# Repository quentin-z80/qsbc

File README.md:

# qsbc

## Specs

- i.MX8M Mini 4x 1.8GHz ARM Cortex-A53
- 4GB LPDDR4
- 4MB QSPI Flash
- 64GB eMMC
- M.2 2230 Slot
- MicroSD card slot
- 2x USB Type-C DRP
- USB Type-C Power in
- USB Type-C debug port
- 10/100/1000 Ethernet
- Displayport output

## Flashing u-boot

1. Get `u-boot`

    ```
    git clone https://gitlab.com/quentin-z80/u-boot.git
    ```

2. Build `TF-A`

    ```
    git clone https://git.trustedfirmware.org/TF-A/trusted-firmware-a.git
    cd trusted-firmware-a
    TF_LDFLAGS="--no-warn-rwx-segment" make plat=imx8mm bl31
    cp build/imx8mm/release/bl31.bin ../u-boot/
    ```

3. Get i.MX8MM DDR Firmware

    ```
    wget https://www.nxp.com/lgfiles/NMG/MAD/YOCTO/firmware-imx-8.9.bin
    chmod +x firmware-imx-8.9.bin
    ./firmware-imx-8.9.bin
    cp firmware-imx-8.9/firmware/ddr/synopsys/lpddr4*.bin u-boot/
    ```

4. Build `u-boot` for SD card boot

    ```
    cd u-boot
    export CROSS_COMPILE=aarch64-linux-gnu- ARCH=arm64
    make qsbc_imx8mm_defconfig
    make
    sudo dd if=flash.bin of=/dev/mmcblk0 bs=1024 seek=32 conv=notrunc
    ```

5. Flash and boot `u-boot` from sd card

    ```
    sudo dd if=flash.bin of=/dev/mmcblk0 bs=1024 seek=32 conv=notrunc
    sudo tio -b 115200 /dev/ttyACM0
    ```

6. Build `u-boot` for QSPI boot

    ```
    make qsbc_imx8mm_fspi_defconfig
    make
    ```

7. Flash `u-boot` to QSPI

    ```
    u-boot=> run dfuspi
    sudo dfu-util -D flash.bin
    ```

## TODO

- USB-UART ICs need to have VDDIO derived from USB VBUS so they do not reset
on board reset (or find a different ic)

- USB VBUS fault pins need to be connected to usb phy oc pads, not gpio pins

- UART1 TXO is connected to the wrong pad

- Test displayport out, waiting for better sn65dsi86 avalability

- optimize bom, replace 0201s with 0402s where there is space / no si limitations

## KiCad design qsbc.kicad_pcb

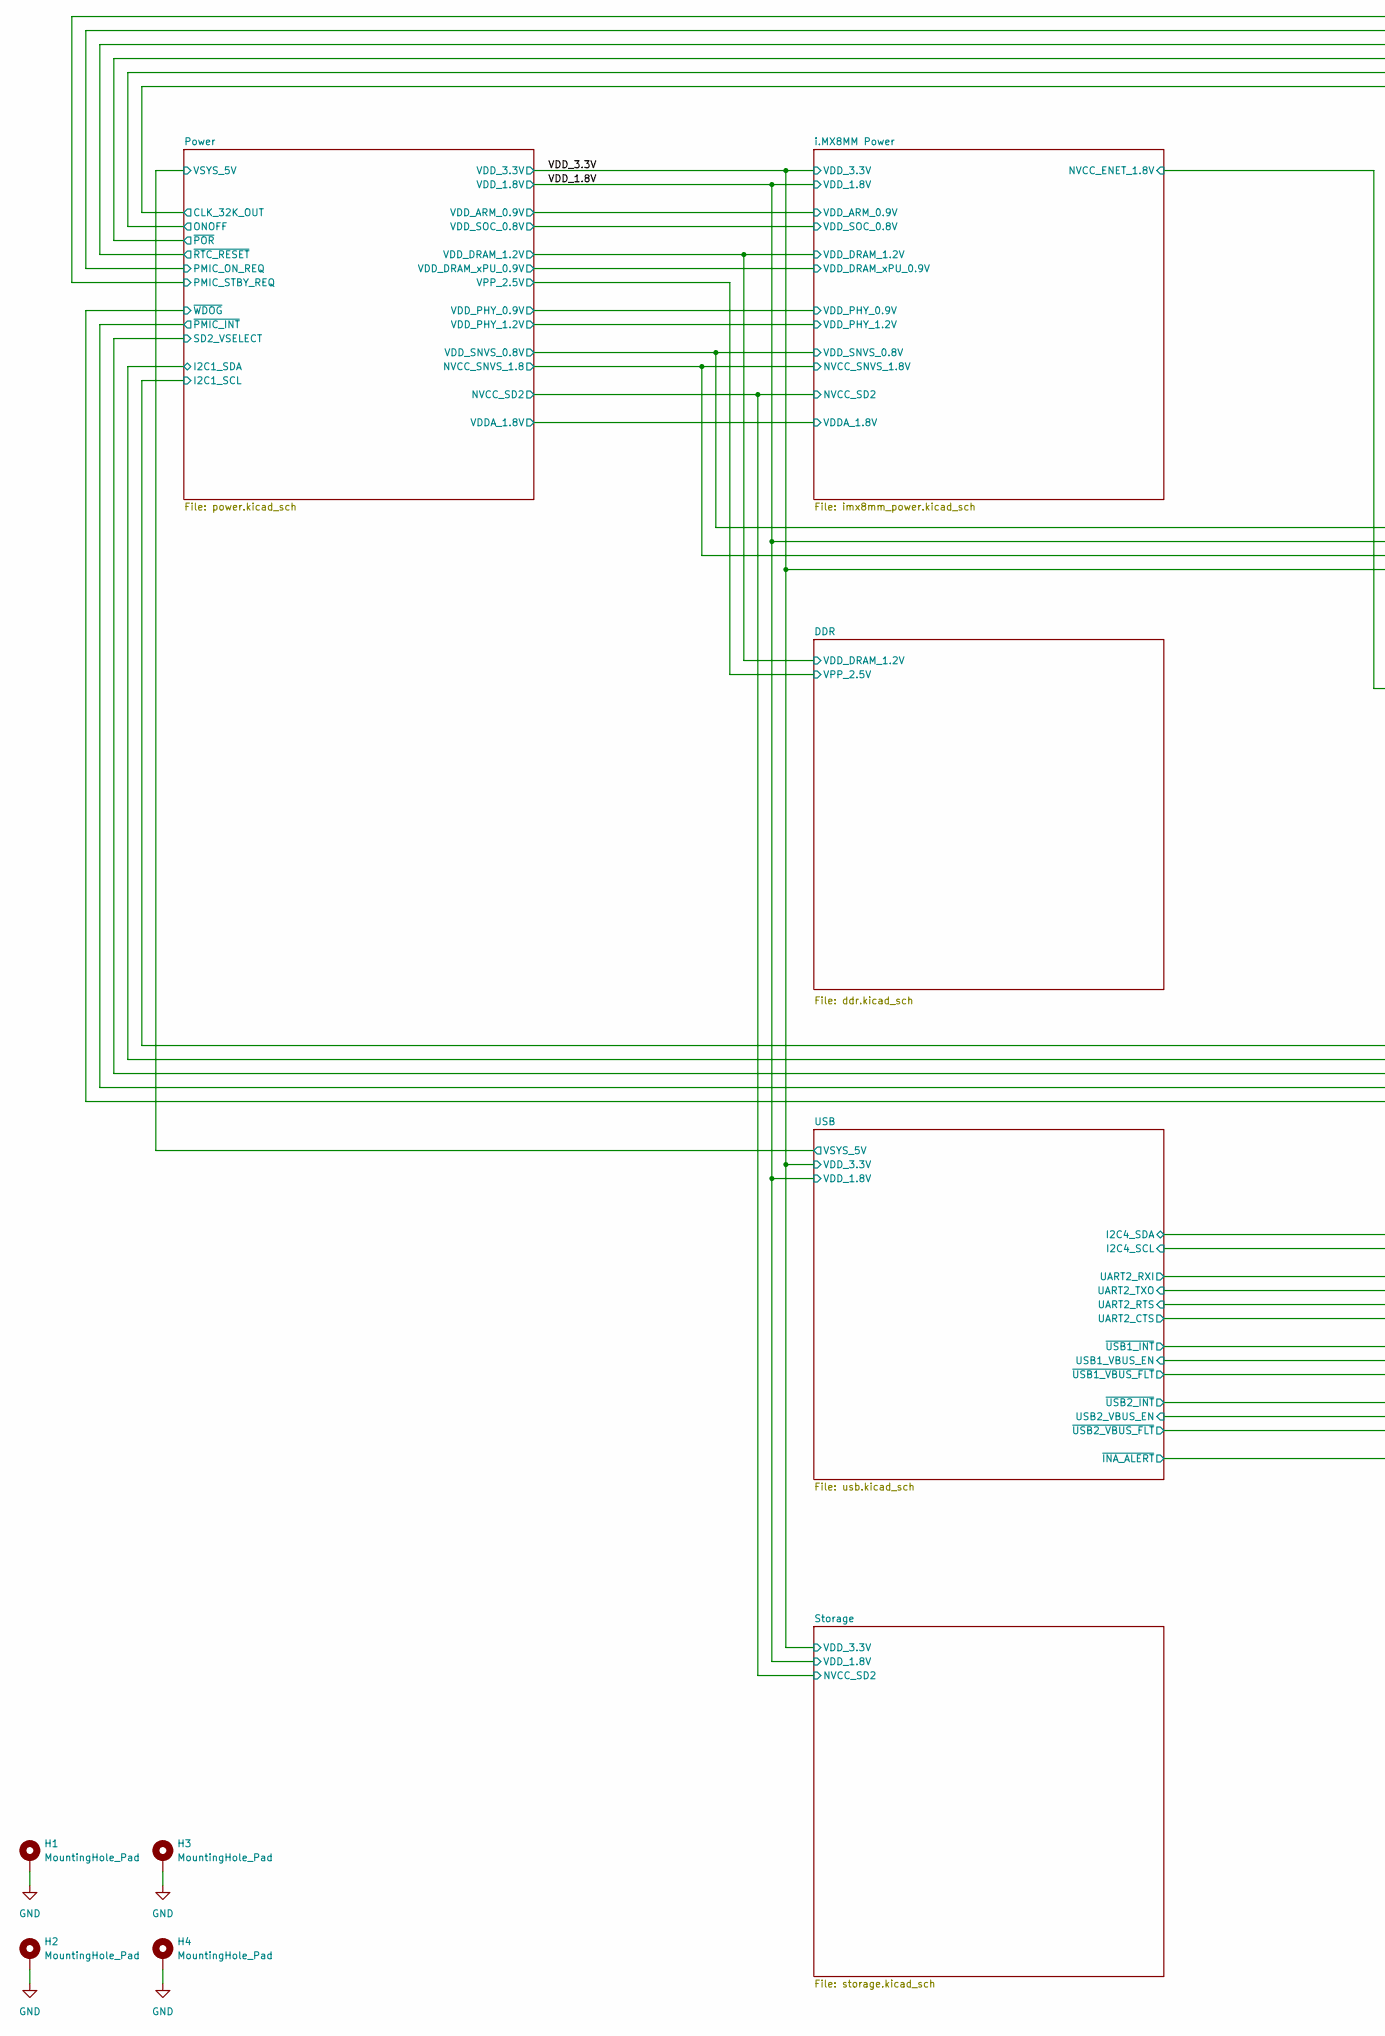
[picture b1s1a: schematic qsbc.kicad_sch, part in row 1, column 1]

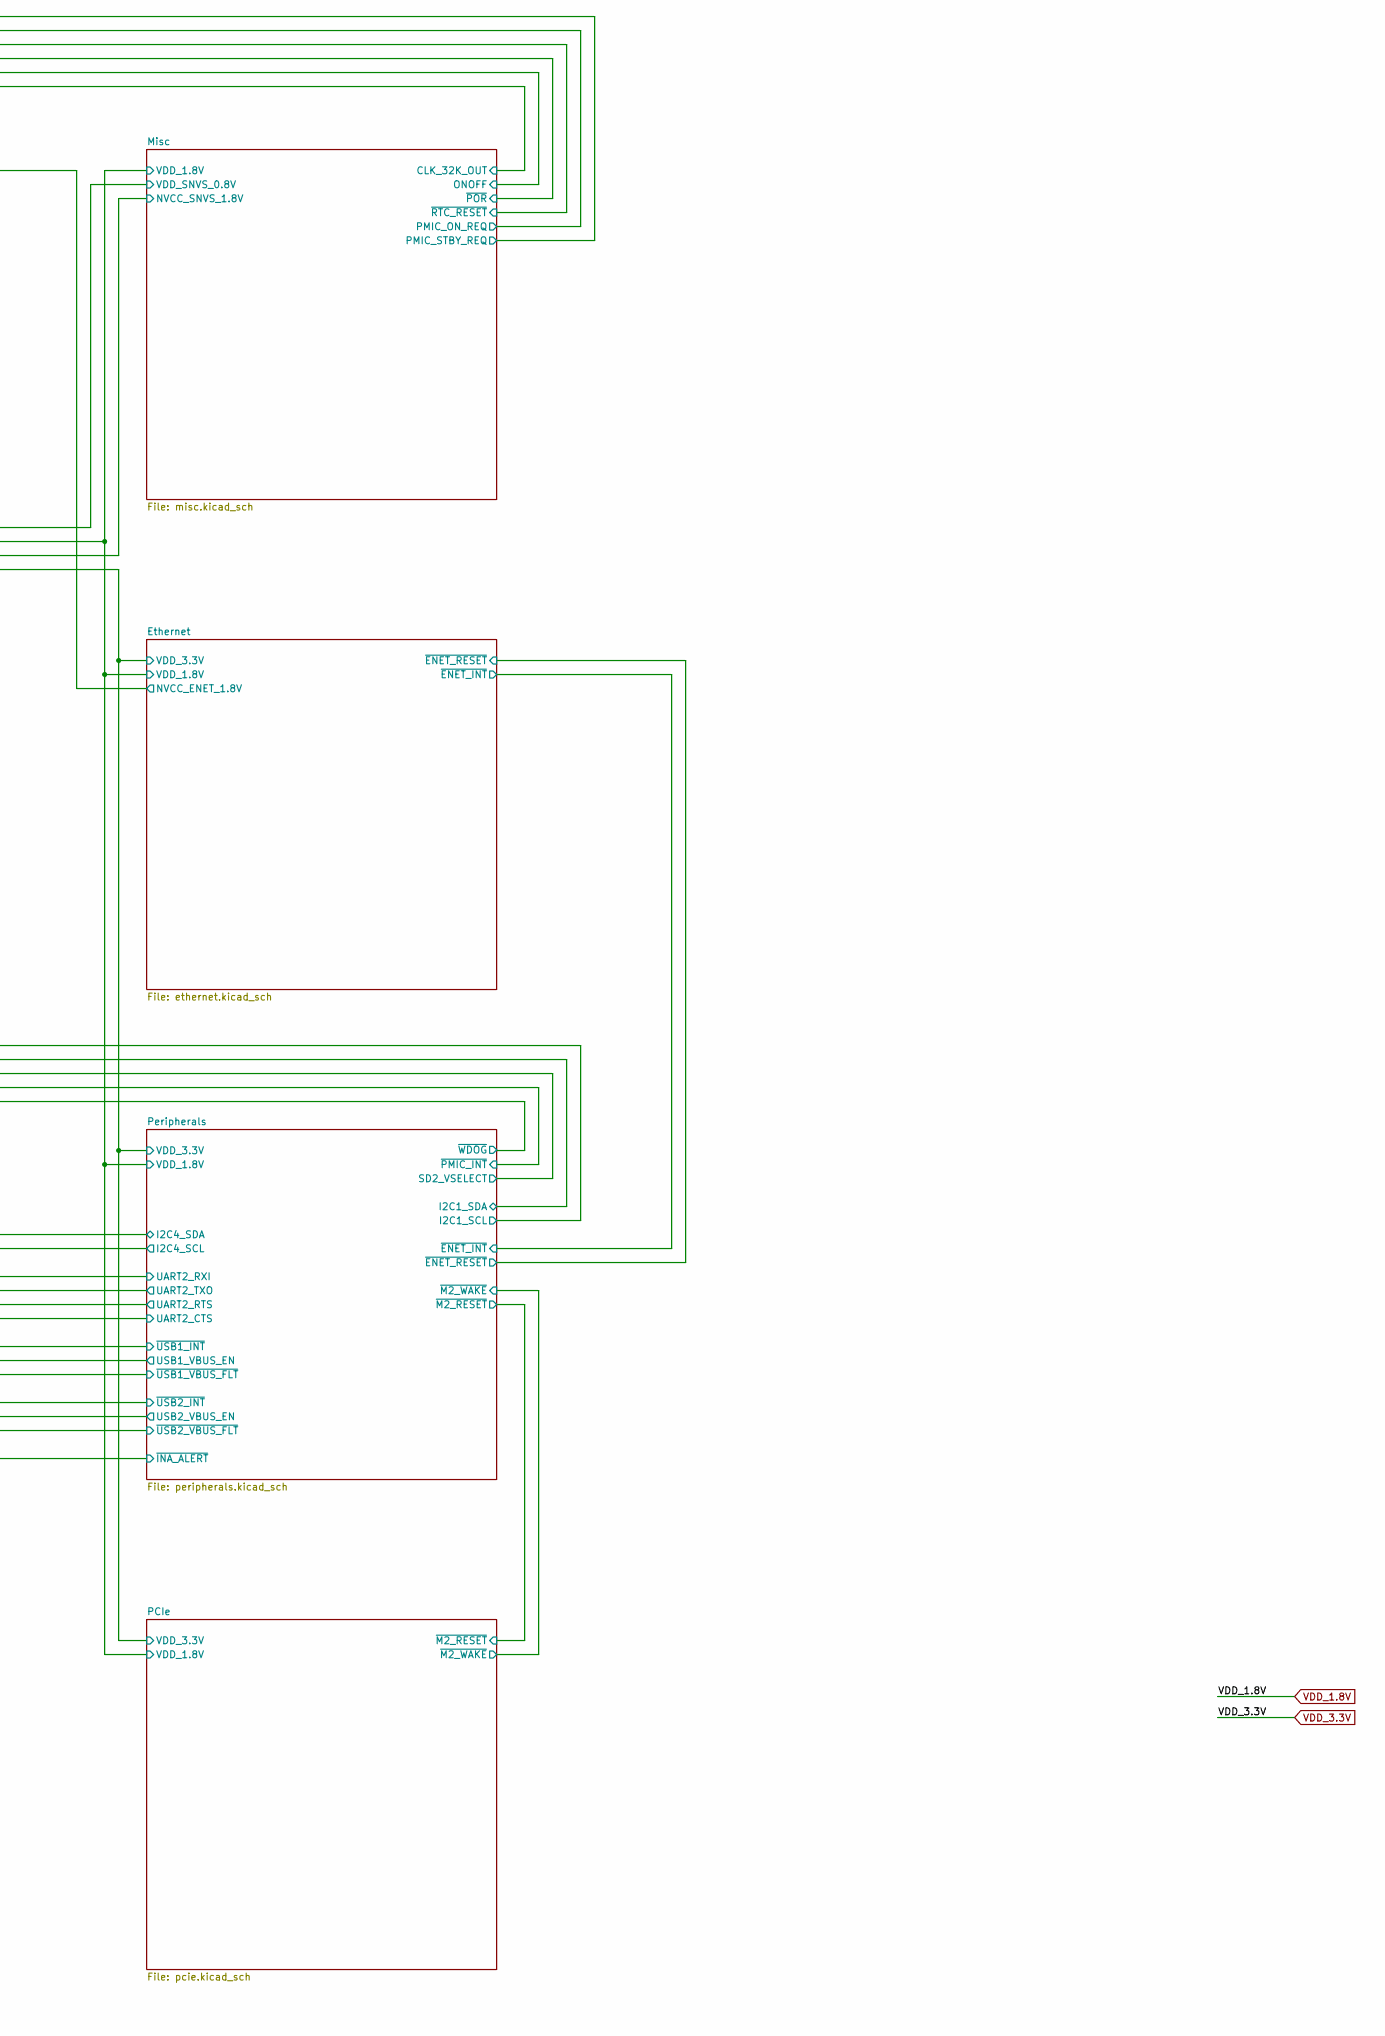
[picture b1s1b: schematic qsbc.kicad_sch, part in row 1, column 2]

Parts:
H1, H2, H3, H4: MountingHole_Pad; MountingHole_3.2mm_M3_Pad_Via

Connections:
GND: H1.1, H2.1, H3.1, H4.1; also elsewhere on the board

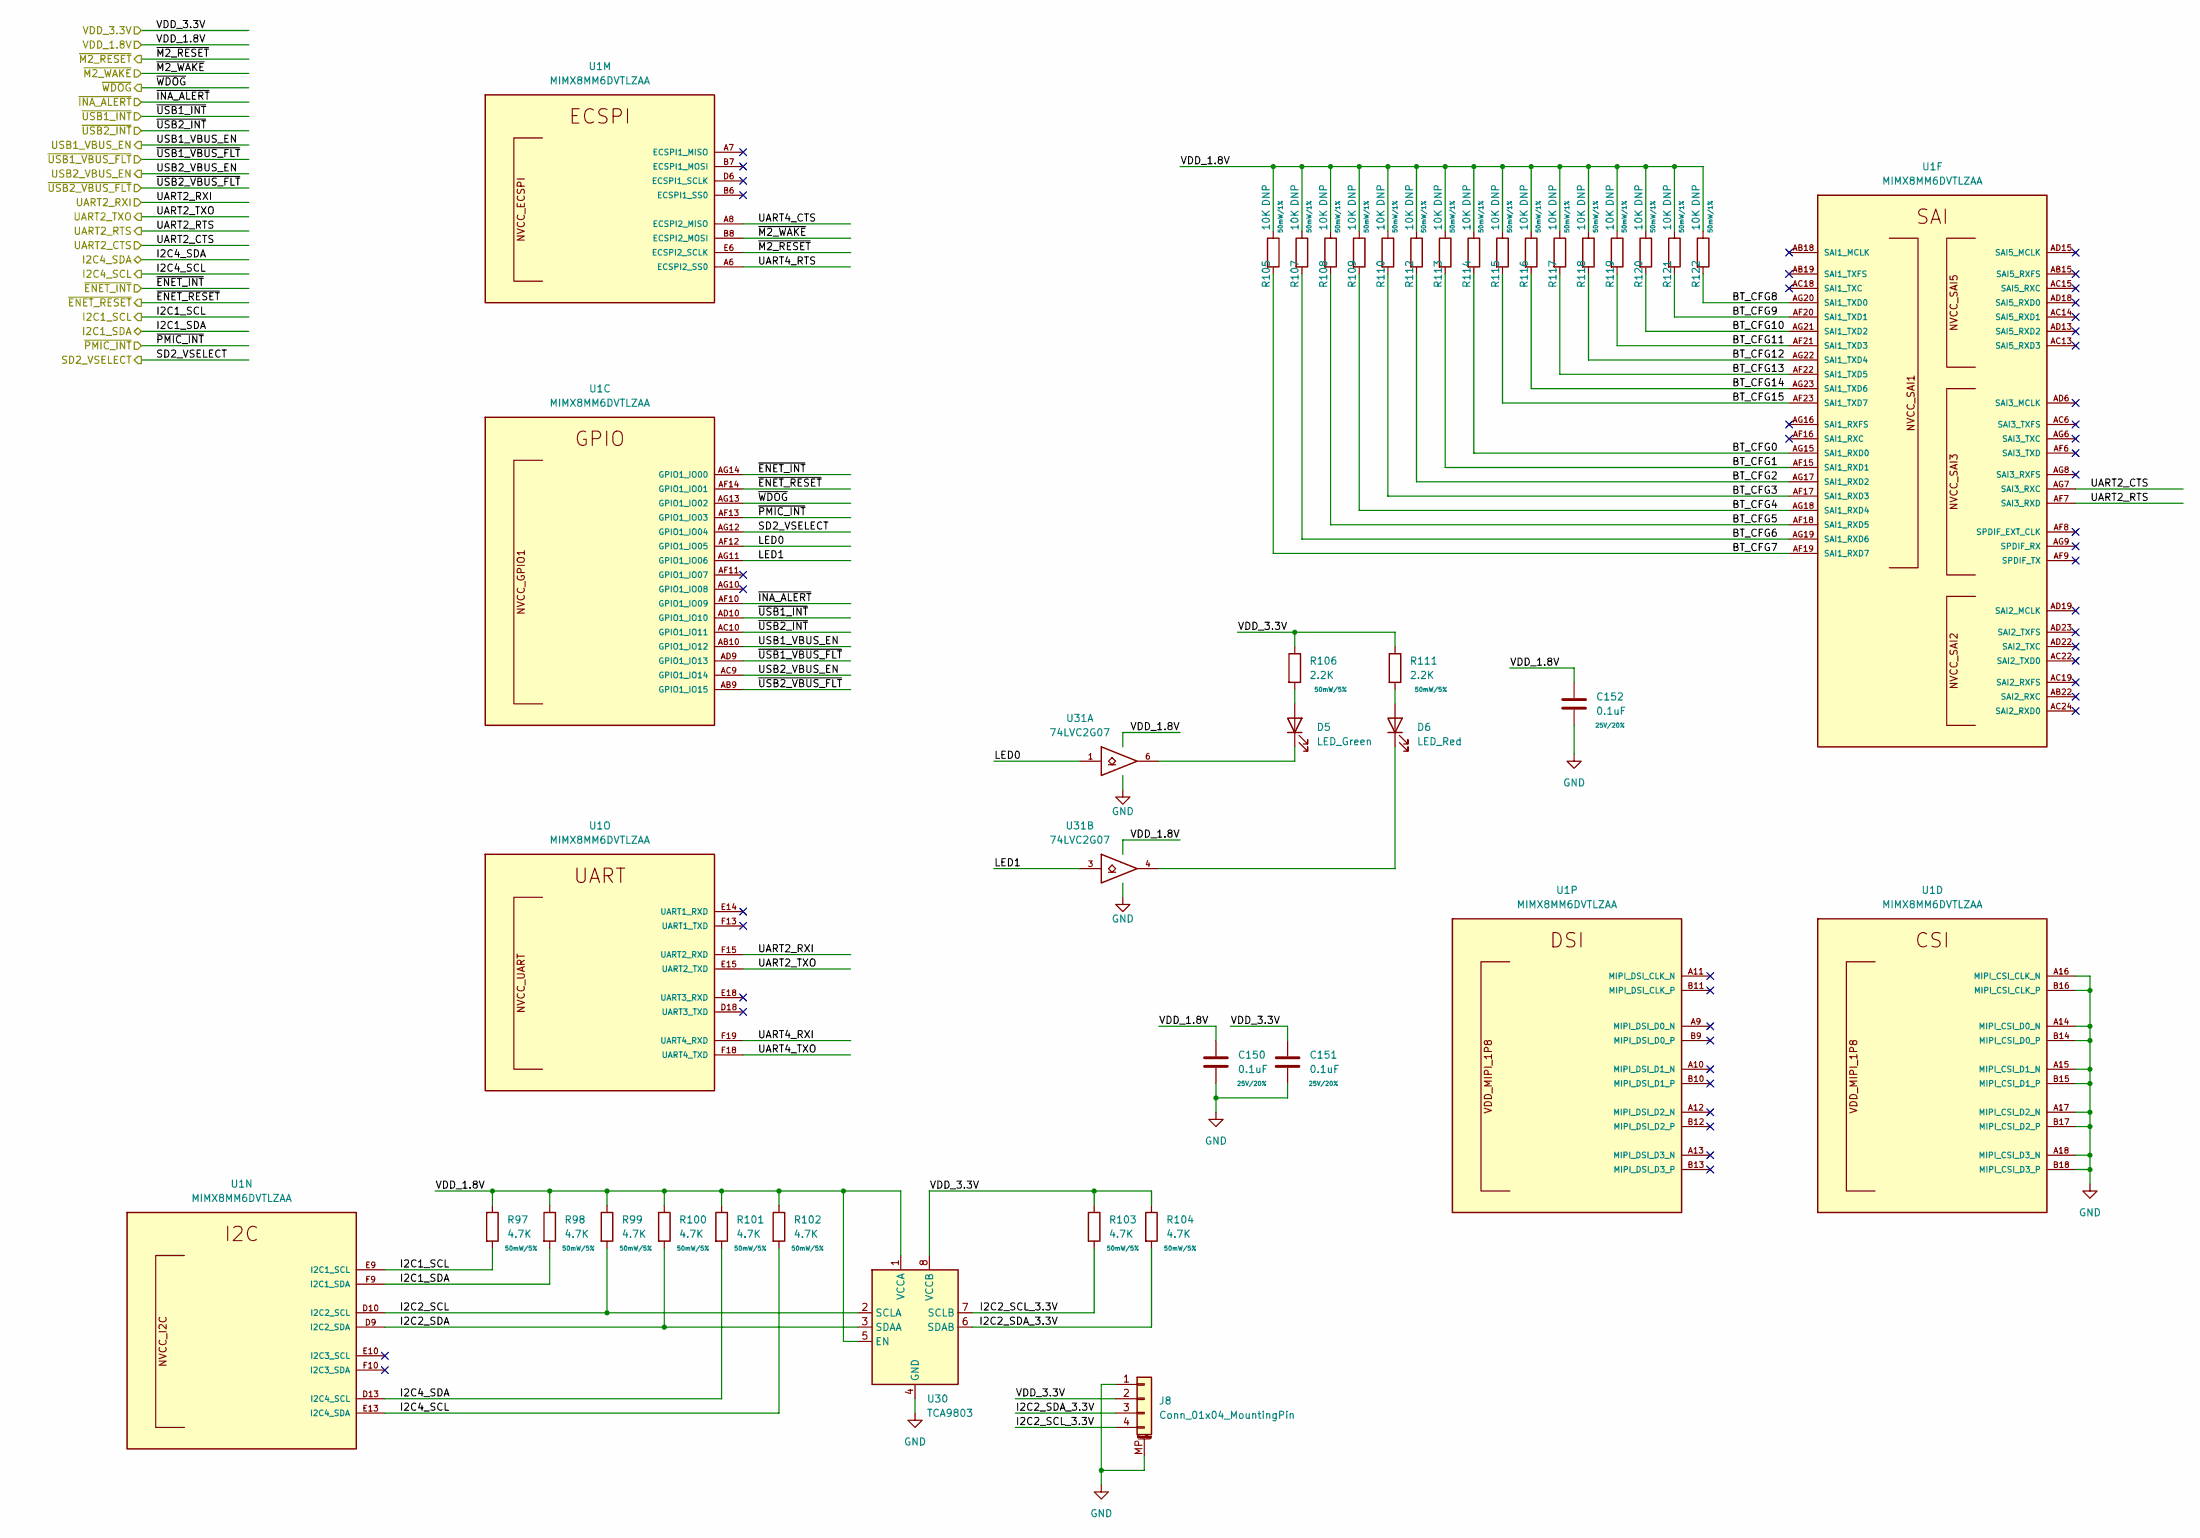
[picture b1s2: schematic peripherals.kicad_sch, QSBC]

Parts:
C150, C151, C152: 0.1uF; C_0402_1005Metric; Rating 25V/20%
D5: LED_Green; LED_0603_1608Metric
D6: LED_Red; LED_0603_1608Metric
J8: Conn_01x04_MountingPin; JST_SH_SM04B-SRSS-TB_1x04-1MP_P1.00mm_Horizontal
R97, R98, R99, R100, R101, R102, R103, R104: 4.7K; R_0402_1005Metric; Rating 50mW/5%
R105, R107, R108, R109, R110, R112, R113, R114, R115, R116, R117, R118, R119, R120, R121, R122: 10K; R_0402_1005Metric; Rating 50mW/1%; MPN RC0402JR-0710KL; DigiKey_PN 311-10KJRCT-ND
R106, R111: 2.2K; R_0402_1005Metric; Rating 50mW/5%
U1: MIMX8MM6DVTLZAA; SOT1967-1
U30: TCA9803; VSSOP-8_3.0x3.0mm_P0.65mm
U31: 74LVC2G07; SOT-886

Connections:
/Ethernet/~ENET_INT: U1.AG14 (GPIO1_IO00); also elsewhere on the board
/Ethernet/~ENET_RESET: U1.AF14 (GPIO1_IO01); also elsewhere on the board
/PCIe/~M2_RESET: U1.E6 (ECSPI2_SCLK); also elsewhere on the board
/PCIe/~M2_WAKE: U1.B8 (ECSPI2_MOSI); also elsewhere on the board
/Peripherals/BT_CFG0: R114.2, U1.AG15 (SAI1_RXD0)
/Peripherals/BT_CFG1: R113.2, U1.AF15 (SAI1_RXD1)
/Peripherals/BT_CFG2: R112.2, U1.AG17 (SAI1_RXD2)
/Peripherals/BT_CFG3: R110.2, U1.AF17 (SAI1_RXD3)
/Peripherals/BT_CFG4: R109.2, U1.AG18 (SAI1_RXD4)
/Peripherals/BT_CFG5: R108.2, U1.AF18 (SAI1_RXD5)
/Peripherals/BT_CFG6: R107.2, U1.AG19 (SAI1_RXD6)
/Peripherals/BT_CFG7: R105.2, U1.AF19 (SAI1_RXD7)
/Peripherals/BT_CFG8: R122.2, U1.AG20 (SAI1_TXD0)
/Peripherals/BT_CFG9: R121.2, U1.AF20 (SAI1_TXD1)
/Peripherals/BT_CFG10: R120.2, U1.AG21 (SAI1_TXD2)
/Peripherals/BT_CFG11: R119.2, U1.AF21 (SAI1_TXD3)
/Peripherals/BT_CFG12: R118.2, U1.AG22 (SAI1_TXD4)
/Peripherals/BT_CFG13: R117.2, U1.AF22 (SAI1_TXD5)
/Peripherals/BT_CFG14: R116.2, U1.AG23 (SAI1_TXD6)
/Peripherals/BT_CFG15: R115.2, U1.AF23 (SAI1_TXD7)
/Peripherals/I2C1_SCL: R97.2, U1.E9 (I2C1_SCL); also elsewhere on the board
/Peripherals/I2C1_SDA: R98.2, U1.F9 (I2C1_SDA); also elsewhere on the board
/Peripherals/I2C2_SCL: R99.2, U1.D10 (I2C2_SCL), U30.2 (SCLA)
/Peripherals/I2C2_SCL_3.3V: J8.4, R103.2, U30.7 (SCLB)
/Peripherals/I2C2_SDA: R100.2, U1.D9 (I2C2_SDA), U30.3 (SDAA)
/Peripherals/I2C2_SDA_3.3V: J8.3, R104.2, U30.6 (SDAB)
/Peripherals/I2C4_SCL: R102.2, U1.E13 (I2C4_SDA); also elsewhere on the board
/Peripherals/I2C4_SDA: R101.2, U1.D13 (I2C4_SCL); also elsewhere on the board
/Peripherals/LED0: U1.AF12 (GPIO1_IO05), U31.1
/Peripherals/LED1: U1.AG11 (GPIO1_IO06), U31.3
/Peripherals/SD2_VSELECT: U1.AG12 (GPIO1_IO04); also elsewhere on the board
/Peripherals/UART2_CTS: U1.AG7 (SAI3_RXC); also elsewhere on the board
/Peripherals/UART2_RTS: U1.AF7 (SAI3_RXD); also elsewhere on the board
/Peripherals/UART2_RXI: U1.F15 (UART2_RXD); also elsewhere on the board
/Peripherals/UART2_TXO: U1.E15 (UART2_TXD); also elsewhere on the board
/Peripherals/UART4_CTS: U1.A8 (ECSPI2_MISO)
/Peripherals/UART4_RTS: U1.A6 (ECSPI2_SS0)
/Peripherals/UART4_RXI: U1.F19 (UART4_RXD)
/Peripherals/UART4_TXO: U1.F18 (UART4_TXD)
/Peripherals/USB1_VBUS_EN: U1.AB10 (GPIO1_IO12); also elsewhere on the board
/Peripherals/USB2_VBUS_EN: U1.AC9 (GPIO1_IO14); also elsewhere on the board
/Peripherals/~INA_ALERT: U1.AF10 (GPIO1_IO09); also elsewhere on the board
/Peripherals/~PMIC_INT: U1.AF13 (GPIO1_IO03); also elsewhere on the board
/Peripherals/~USB1_INT: U1.AD10 (GPIO1_IO10); also elsewhere on the board
/Peripherals/~USB1_VBUS_FLT: U1.AD9 (GPIO1_IO13); also elsewhere on the board
/Peripherals/~USB2_INT: U1.AC10 (GPIO1_IO11); also elsewhere on the board
/Peripherals/~USB2_VBUS_FLT: U1.AB9 (GPIO1_IO15); also elsewhere on the board
/Peripherals/~WDOG: U1.AG13 (GPIO1_IO02)
GND: C150.2, C151.2, C152.2, J8.1, J8.MP (MountPin), U1.A14 (MIPI_CSI_D0_N), U1.A15 (MIPI_CSI_D1_N), U1.A16 (MIPI_CSI_CLK_N), U1.A17 (MIPI_CSI_D2_N), U1.A18 (MIPI_CSI_D3_N), U1.B14 (MIPI_CSI_D0_P), U1.B15 (MIPI_CSI_D1_P), U1.B16 (MIPI_CSI_CLK_P), U1.B17 (MIPI_CSI_D2_P), U1.B18 (MIPI_CSI_D3_P), U30.4 (GND), U31.2 (GND); also elsewhere on the board
unnamed: D5.1 (K), U31.6
unnamed: D5.2 (A), R106.2
unnamed: D6.1 (K), U31.4
unnamed: D6.2 (A), R111.2
VDD_1.8V: C150.1, C152.1, R97.1, R98.1, R99.1, R100.1, R101.1, R102.1, R105.1, R107.1, R108.1, R109.1, R110.1, R112.1, R113.1, R114.1, R115.1, R116.1, R117.1, R118.1, R119.1, R120.1, R121.1, R122.1, U30.1 (VCCA), U30.5 (EN), U31.5 (VCC); also elsewhere on the board
VDD_3.3V: C151.1, J8.2, R103.1, R104.1, R106.1, R111.1, U30.8 (VCCB); also elsewhere on the board

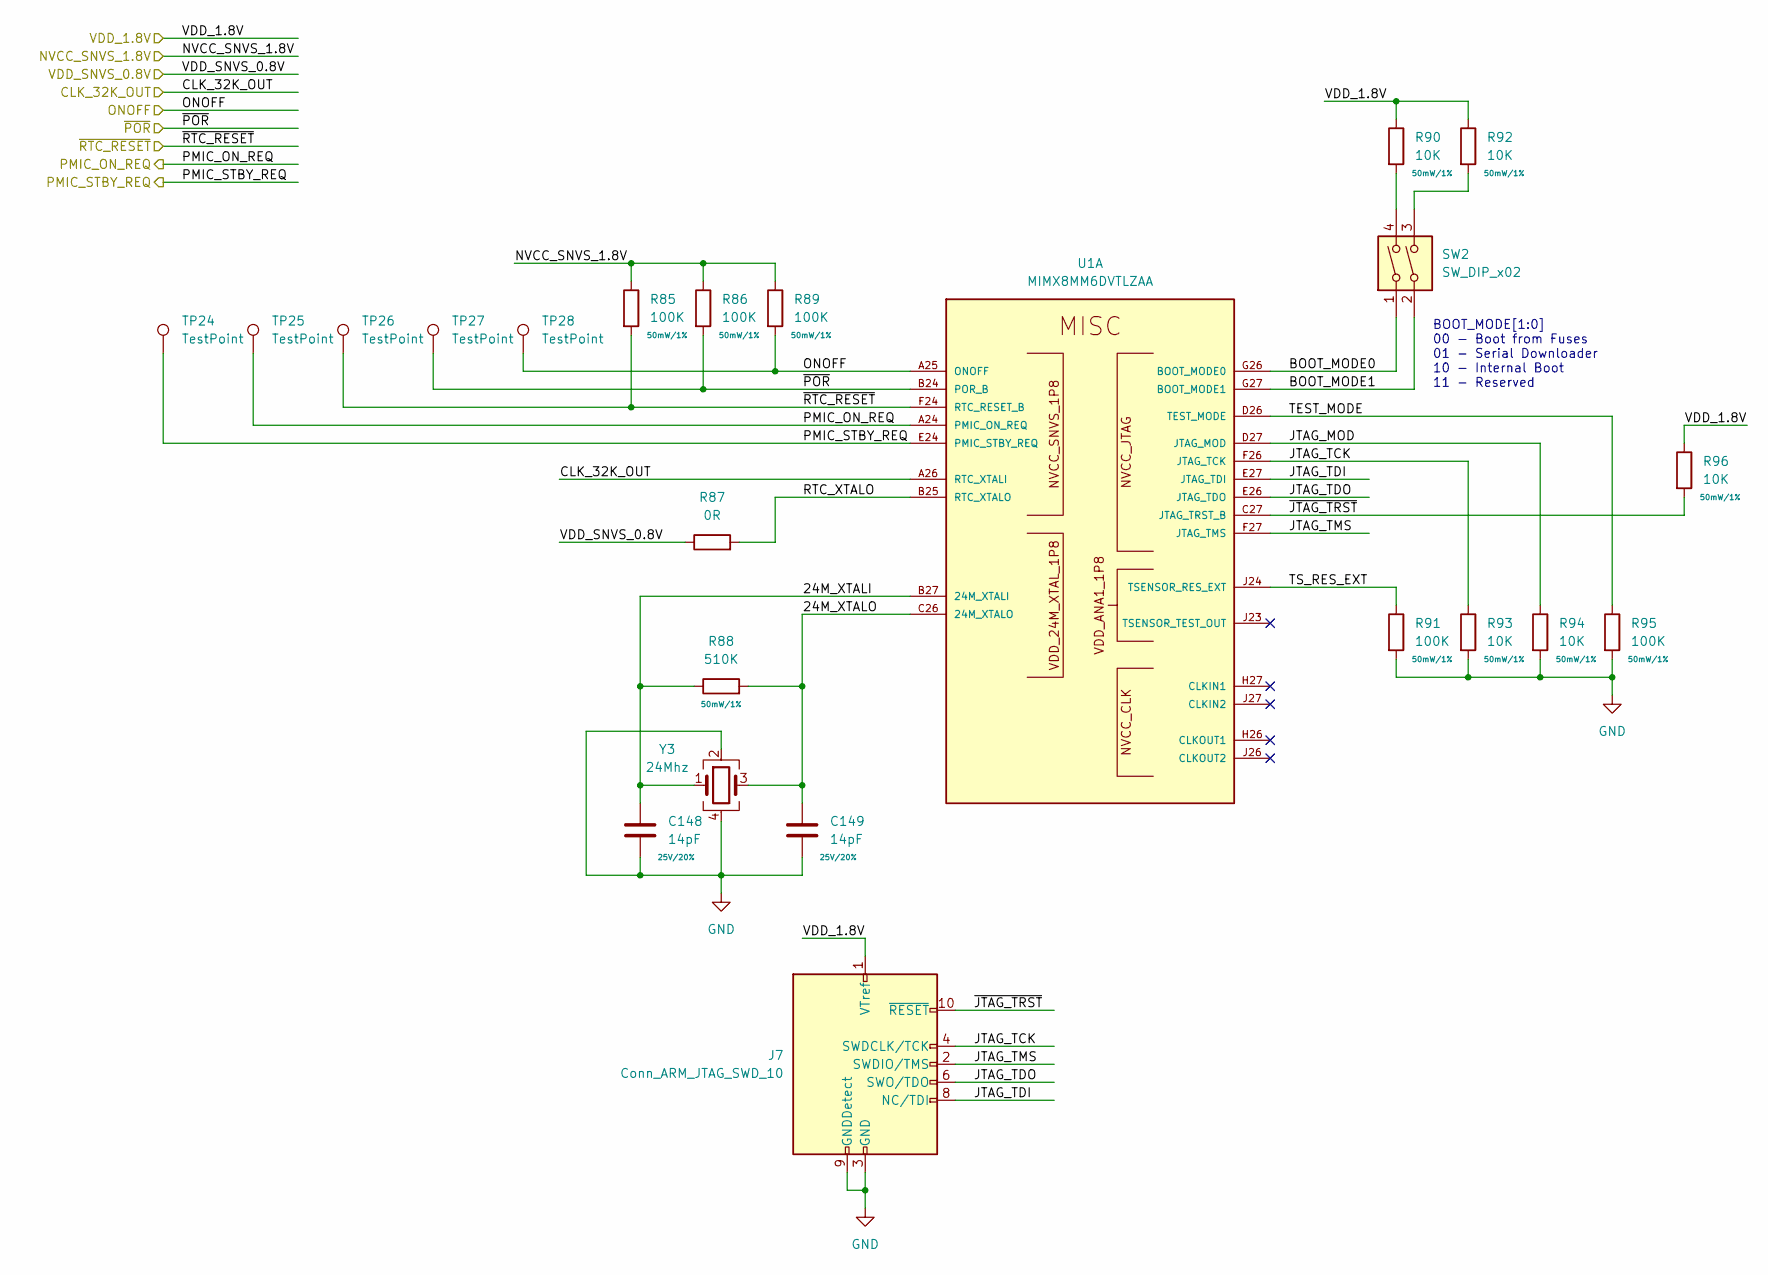
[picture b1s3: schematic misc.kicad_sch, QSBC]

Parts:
C148, C149: 14pF; C_0402_1005Metric; Rating 25V/20%
J7: Conn_ARM_JTAG_SWD_10; PinHeader_2x05_P1.27mm_Vertical
R85, R86, R89, R91, R95: 100K; R_0402_1005Metric; Rating 50mW/1%
R87: 0R; R_0402_1005Metric
R88: 510K; R_0402_1005Metric; Rating 50mW/1%
R90, R92, R93, R94, R96: 10K; R_0402_1005Metric; Rating 50mW/1%
SW2: SW_DIP_x02; DHN-02
TP24, TP25, TP26, TP27, TP28: TestPoint; TestPoint_Pad_D1.0mm
U1: MIMX8MM6DVTLZAA; SOT1967-1
Y3: 24Mhz; Crystal_SMD_3225-4Pin_3.2x2.5mm; MPN ECS-240-10-33B-7KM-TR

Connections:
/Misc/24M_XTALI: C148.1, R88.1, U1.B27 (24M_XTALI), Y3.1
/Misc/24M_XTALO: C149.1, R88.2, U1.C26 (24M_XTALO), Y3.3
/Misc/BOOT_MODE0: SW2.1, U1.G26 (BOOT_MODE0)
/Misc/BOOT_MODE1: SW2.2, U1.G27 (BOOT_MODE1)
/Misc/CLK_32K_OUT: U1.A26 (RTC_XTALI); also elsewhere on the board
/Misc/JTAG_MOD: R94.1, U1.D27 (JTAG_MOD)
/Misc/JTAG_TCK: J7.4 (SWDCLK/TCK), R93.1, U1.F26 (JTAG_TCK)
/Misc/JTAG_TDI: J7.8 (NC/TDI), U1.E27 (JTAG_TDI)
/Misc/JTAG_TDO: J7.6 (SWO/TDO), U1.E26 (JTAG_TDO)
/Misc/JTAG_TMS: J7.2 (SWDIO/TMS), U1.F27 (JTAG_TMS)
/Misc/NVCC_SNVS_1.8V: R85.1, R86.1, R89.1; also elsewhere on the board
/Misc/ONOFF: R89.2, TP28.1, U1.A25 (ONOFF); also elsewhere on the board
/Misc/PMIC_ON_REQ: TP25.1, U1.A24 (PMIC_ON_REQ); also elsewhere on the board
/Misc/PMIC_STBY_REQ: TP24.1, U1.E24 (PMIC_STBY_REQ); also elsewhere on the board
/Misc/RTC_XTALO: R87.2, U1.B25 (RTC_XTALO)
/Misc/TEST_MODE: R95.1, U1.D26 (TEST_MODE)
/Misc/TS_RES_EXT: R91.1, U1.J24 (TSENSOR_RES_EXT)
/Misc/VDD_SNVS_0.8V: R87.1; also elsewhere on the board
/Misc/~JTAG_TRST: J7.10 (~RESET), R96.2, U1.C27 (JTAG_TRST_B)
/Misc/~POR: R86.2, TP27.1, U1.B24 (POR_B); also elsewhere on the board
/Misc/~RTC_RESET: R85.2, TP26.1, U1.F24 (RTC_RESET_B); also elsewhere on the board
GND: C148.2, C149.2, J7.3 (GND), J7.5 (GND), J7.9 (GNDDetect), R91.2, R93.2, R94.2, R95.2, Y3.2, Y3.4; also elsewhere on the board
unnamed: R90.2, SW2.4
unnamed: R92.2, SW2.3
VDD_1.8V: J7.1 (VTref), R90.1, R92.1, R96.1; also elsewhere on the board

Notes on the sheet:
BOOT_MODE[1:0] 00 - Boot from Fuses 01 - Serial Downloader 10 - Internal Boot 11 - Reserved
